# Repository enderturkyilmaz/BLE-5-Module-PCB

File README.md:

# BLE-5-Module-PCB
This PCB is designed for long range advertising. The Led shows if the module advertises or not.

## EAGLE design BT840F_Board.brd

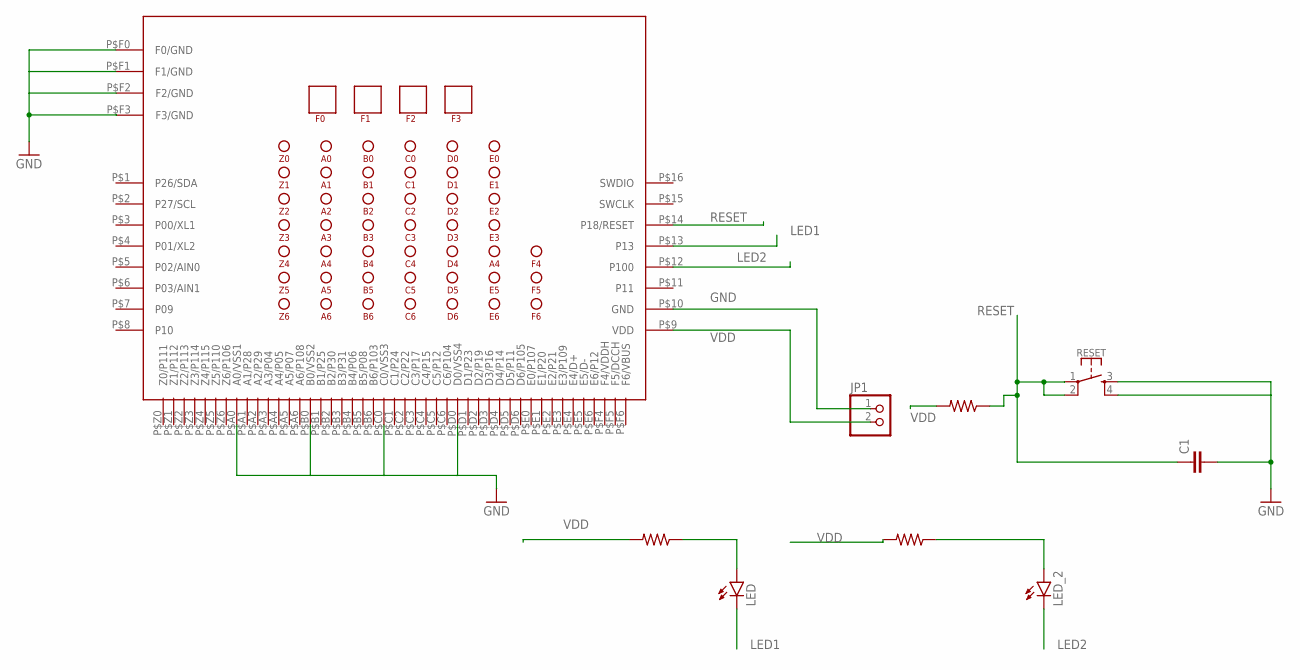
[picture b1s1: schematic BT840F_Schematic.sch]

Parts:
C1: C-EUC0805; C0805
JP1: PINHD-1X2; 1X02
LED: LEDCHIP-LED0805; CHIP-LED0805
LED_2: LEDCHIP-LED0805; CHIP-LED0805
RESET: MOMENTARY-SWITCH-SPST-2-SMD-4.6X2.8MM; TACTILE_SWITCH_SMD_4.6X2.8MM
R_LED1, R_LED2: 4.7k; R0805
R_RESET: 4.7k; R0805
U1: BT840

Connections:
GND: C1.2, JP1.1, RESET.3, RESET.4, U1.P$10 (GND), U1.P$A0 (A0/VSS1), U1.P$B0 (B0/VSS2), U1.P$C0 (C0/VSS3), U1.P$D0 (D0/VSS4), U1.P$F0 (F0/GND), U1.P$F1 (F1/GND), U1.P$F2 (F2/GND), U1.P$F3 (F3/GND)
LED1: LED.C, U1.P$13 (P13)
LED2: LED_2.C, U1.P$12 (P100)
unnamed: LED_2.A, R_LED2.1
unnamed: LED.A, R_LED1.1
RESET: C1.1, RESET.1, RESET.2, R_RESET.1, U1.P$14 (P18/RESET)
VDD: JP1.2, R_LED1.2, R_LED2.2, R_RESET.2, U1.P$9 (VDD)

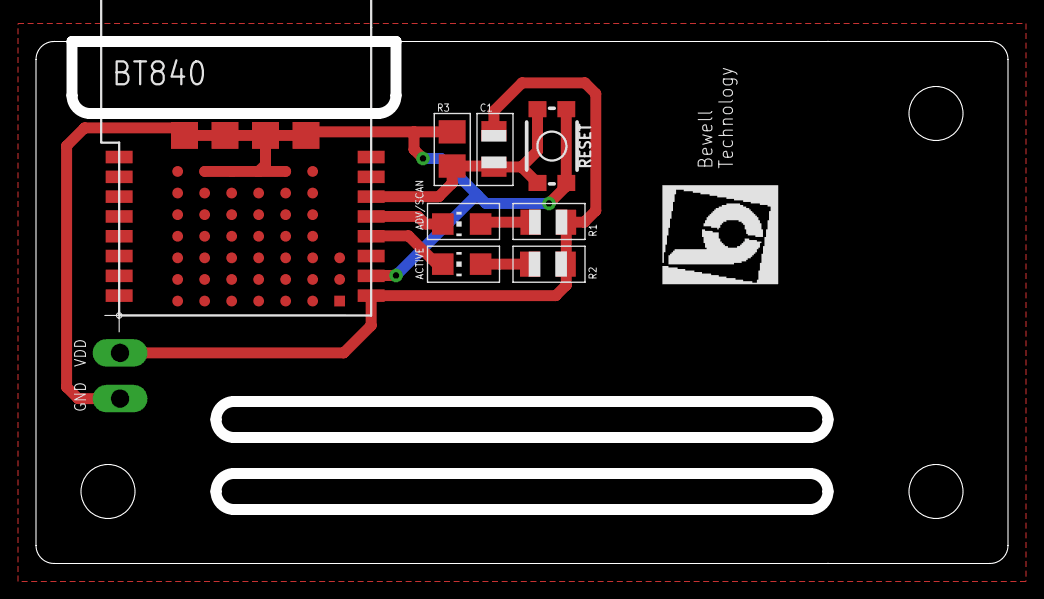
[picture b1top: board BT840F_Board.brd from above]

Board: 2 copper layers, 53.4 x 28.7 mm, 9 parts (1 on the bottom side), 7 nets.

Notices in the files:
parts and their libraries:
SparkFun-Switches: Licensing: Creative Commons ShareAlike 4.0 International - https://creativecommons.org/licenses/by-sa/4.0
